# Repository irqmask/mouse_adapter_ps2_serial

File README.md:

# PS/2 to serial mouse adapter

This is an intelligent adapter to connect PS/2 mouses to serial mouses uses in the 80s and 90s.
Hope to help some retro-computer enthusiasts connecting a "more modern" mouse to theold PC.

Currently tested with 2-button ball mouses. Untested with optical mouses, yet.

I made this for fun, use this software and self-built hardware at your own risk (and with great fun)!

# Hardware

The hardware basically consists of a ATtiny2313 microcontroller and a MAX232 level shifter. The PS/2 is connected to the INT0 and INT1 pins of the ATtiny2313. The internal pull-up resistors are used for the idle state. 

The serial mouse is connected via a MAX232 to the UART of the ATtiny2313.
The schematics will give more details.

This is the first prototype.

The PS/2 connection is matching the connector of the PS/2 connector bracket which I found in an assortment of old computer cables.

The RS232 connection for the mouse is a 1:1 connection between the Pin-header and the DB9 connector.
This allows to mount it inside an old PC and connect it directly to the interface card. 

Do not use the type of DB9 connectors which are crimped directly onto the cable! 

# Software

## How to build and program

First the assembler source code must be assembled into a hex file, then it can
be programmed to the microcontroller.

For assembling I use avr-gcc and avrdude under Ubuntu Linux

To install the assembler, simply execute

    sudo apt install gcc-avr avr-libc avrdude
    
To assemble the microcontroller software execute:

    cd sw/
    make
    
To program the device, avrdude is used with the AVR ISP mk2 programmer.
The fuses of the controller need to be programmed:

    avrdude -c avrispmkII -p t2313 -U lfuse:w:0xEE:m -U hfuse:w:0xDF:m -U efuse:w:0xFF:m

The assembled hex file is programmed like this:

    avrdude -c avrispmkII -p t2313 -e -U flash:w:mouse.hex -U flash:v:mouse.hex

or simply

    make program

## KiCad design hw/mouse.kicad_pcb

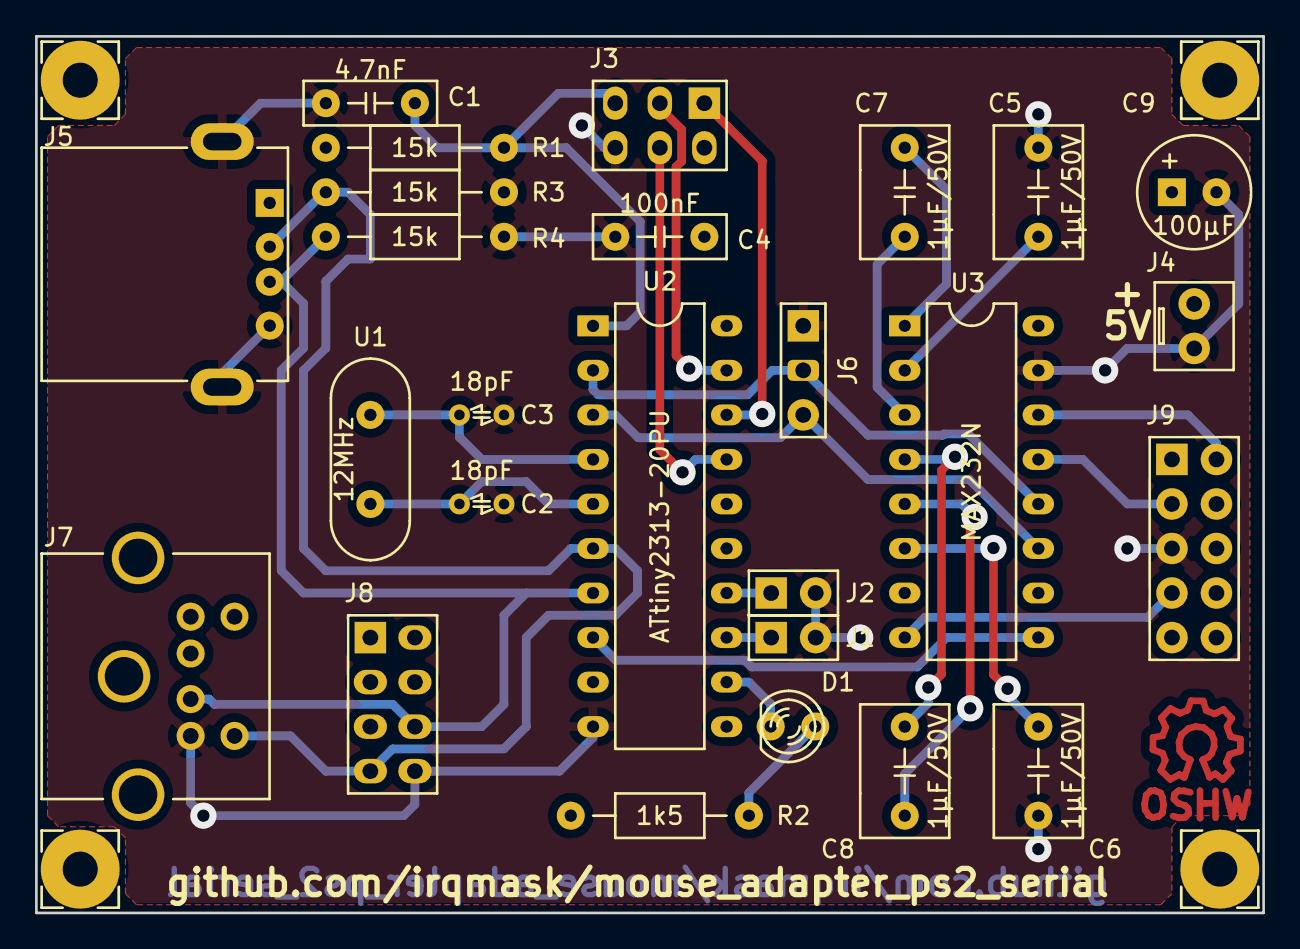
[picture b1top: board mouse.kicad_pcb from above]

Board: 2 copper layers, 70.0 x 50.0 mm, 31 parts (0 on the bottom side), 26 nets.

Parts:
C1: 4,7nF; C_RM5.08mm_5x2.5mm
C2, C3: 18pF; C_CER_2.54mm
C4: 100nF; C_RM5.08mm_5x2.5mm
C5, C6, C7, C8: 1µF/50V; C_RM5.08mm_5x5mm
C9: 100µF; CP_RM2.54mm_D6.5mm
D1: LED gr 2mA, 1,9V; LED_RM2.54mm_D3mm
HOLE_2.5mm, HOLE_2.5mm#2, HOLE_2.5mm#3, HOLE_2.5mm#4: VAL**; HOLE_2mm
J1: J1; HEADER_2x1
J2: J2; HEADER_2x1
J3: CONN-ISP-6; HEADER_3x2
J4: CONN_2X1; PCB_CON2
J5: CONN_5X1; USB_A
J6: CONN_3X1; HEADER_3x1
J7: Mini-DIN-6; MiniDIN_6pole
J8: CONN_4X2; HEADER_4x2
J9: CONN_5X2; HEADER_5x2
LOGO1: OPEN_HARDWARE_1; Symbol_OSHW-Logo_Copper
R1, R3, R4: 15k; R_RM10.16mm
R2: 1k5; R_RM10.16mm
U1: 12MHz; CRY_HC49
U2: ATtiny2313-20PU; DIP20
U3: MAX232N; DIP16

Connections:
+5V: C4.1, C9.1, J3.2, J4.2, J5.1, J7.4, J8.2, R1.1, R2.1, U2.20, U3.16
/MCLK: J5.2, J7.5, J8.7, R3.1, U2.6
/MDTA: J5.3, J7.1, J8.6, R4.1, U2.7
/MISO: J3.1, U2.18
/MOSI: J3.4, U2.17
/RESET: C1.2, J3.5, R1.2, U2.1
/RTS: U2.8, U3.9
/RXD: J6.2, U2.2, U3.12
/SCL: J3.3, U2.19
/TXD: J6.3, U2.3, U3.11
GND: C1.1, C2.1, C3.1, C4.2, C5.1, C6.1, C9.2, J1.2, J2.2, J3.6, J4.1, J5.4, J5.5, J6.1, J7.3, J8.8, J9.5, R3.2, R4.2, U2.10, U3.15
unnamed: C2.2, U1.2, U2.5
unnamed: C3.2, U1.1, U2.4
unnamed: C5.2, U3.2
unnamed: C6.2, U3.6
unnamed: C7.1, U3.3
unnamed: C7.2, U3.1
unnamed: C8.1, U3.4
unnamed: C8.2, U3.5
unnamed: D1.1, R2.2
unnamed: D1.2, U2.12
unnamed: J1.1, U2.13
unnamed: J2.1, U2.14
unnamed: J9.2, U3.14
unnamed: J9.3, U3.13
unnamed: J9.7, U3.8

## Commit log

2021-06-23 Initial version.
2021-06-23 Fixed EMail address
2021-06-23 Move hardware one folder up, add pictures for documentation
2021-06-24 Add brief hardware description
2021-12-31 Converted code to GNU assembler and added Makefile
2021-12-31 add PS/2 analyzer tool
    read host and device data from PS/2 port without disturbing transmissing and
    print it as ASCII text on the serial port at 57600bd.
2022-01-01 Provide minor fixes and code cleanup
    minor fixes:
    * output 0 and CR LF in the beginning
    * limit number of bytes stored to array length
    cleanup:
    * deactivated pull-up resistors, since the analyzer must not disturb the bus
    * changed fuses (activate browout detection, change startup)
2022-01-01 Removed empty lines
2022-01-01 Bug fix and cleanup after merging to avrgcc as assembler
    Bugfix
    * fixed naming of interrupts
    * removed BAUD definition from Makefile
    Cleanup
    * move PS2 code into own source file
    * delete spaces at end of line
2022-01-01 Increase timeout between bytes
    old KVM switch inserts bigger break between bytes
2022-01-02 Initial version of PCB layout (still work in progress)
2022-01-02 add Kicad PCB
2022-01-02 add mounting plate done in Freecad
2022-01-02 add PCB gerber files
2022-01-02 Make PDFs and JPEGS of schematic and PCB
2022-01-02 add Freecad drawing fot pcb holder for PC slot-bracket
2022-01-02 removed backup file
2022-12-26 Update software build instructions
2023-06-01 Create makefile.yml to build firmware online
2023-06-01 Fix avr-gcc package name in README.md
